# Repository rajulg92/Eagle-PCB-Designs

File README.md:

# Eagle-PCB-Designs
This Folder contains PCB designs both layout and Schematics for different Robotics sensors and Actuator interfaces. For example Pneumatics, Solenoid Valves, DC Motors and Drivers, BLDC Motors, Maxon Motors, PS2 Remote, etc.

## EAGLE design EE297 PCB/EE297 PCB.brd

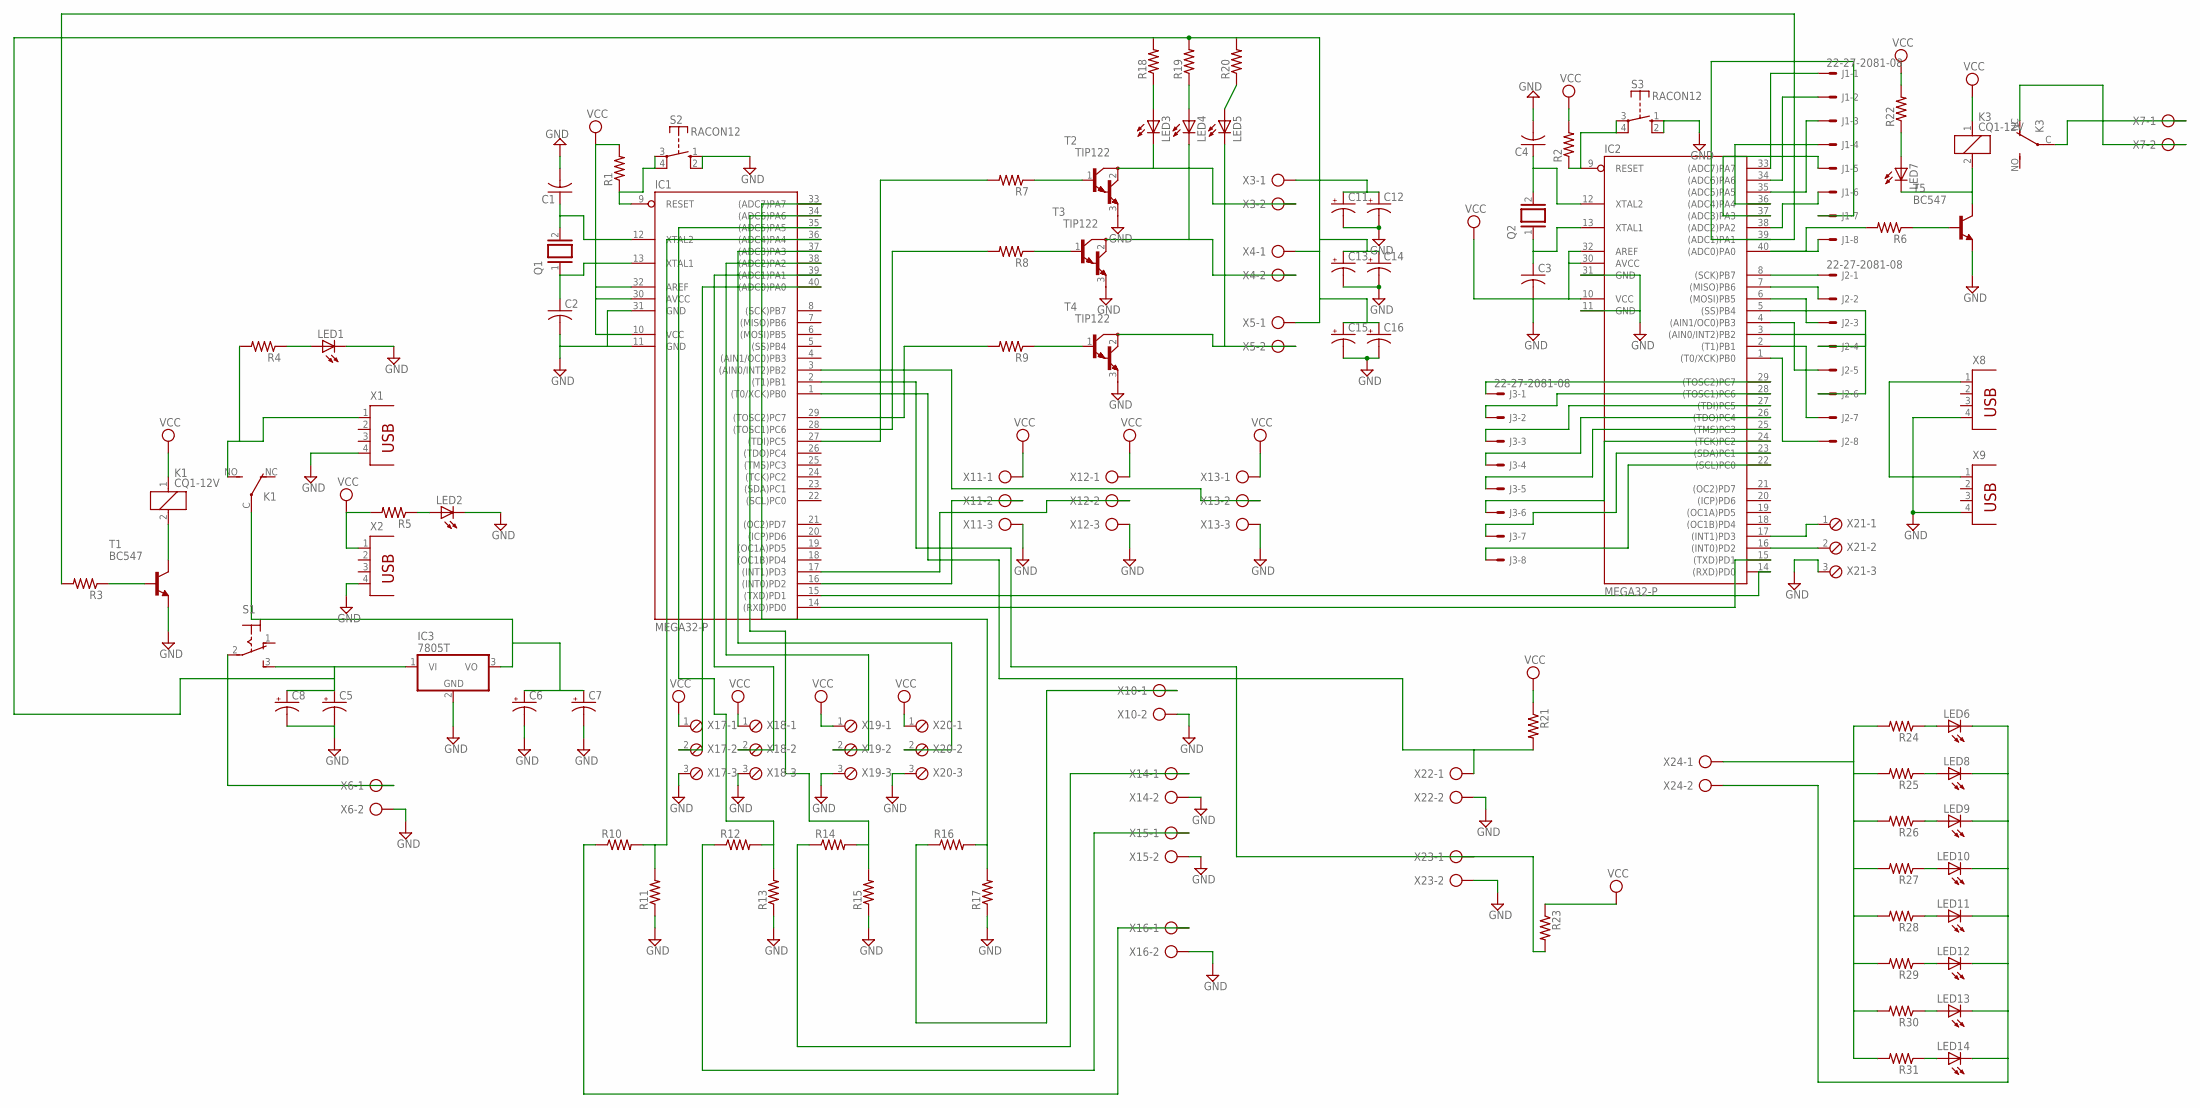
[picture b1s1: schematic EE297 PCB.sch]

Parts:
C1, C2, C3, C4: C-US050H075X075; C050H075X075
C5, C6, C7, C8, C11, C12, C13, C14, C15, C16: CPOL-USE7.5-18; E7,5-18
IC1, IC2: MEGA32-P; DIL40
IC3: 7805T; TO220H
J1, J2, J3: 22-27-2081-08; 6410-08
K1, K3: CQ1-12V; CQ1
LED1, LED2, LED3, LED4, LED5, LED6, LED7, LED8, LED9, LED10, LED11, LED12, LED13, LED14: LED5MM
Q1, Q2: XTAL; Q
R1, R2, R3, R4, R5, R6, R7, R8, R9, R10, R11, R12, R13, R14, R15, R16, R17, R18, R19, R20, R21, R22, R23, R24, R25, R26, R27, R28, R29, R30, R31: R-US_0207/10; 0207/10
S1: 320-916
S2, S3: RACON12
T1, T5: BC547; TO92
T2, T3, T4: TIP122; TO220
X1, X2, X8, X9: PN87520
X3, X4, X5, X6, X7, X10, X14, X15, X16, X22, X23, X24: AK300/2
X11, X12, X13: AK300/3
X17, X18, X19, X20, X21: MPT3; 3POL254

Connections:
GND: C1.2, C2.2, C3.2, C4.2, C5.-, C6.-, C7.-, C8.-, C11.-, C12.-, C13.-, C14.-, C15.-, C16.-, IC1.11 (GND), IC1.31 (GND), IC3.2 (GND), LED1.K (C), LED2.K (C), R11.1, R13.1, R15.1, R17.1, S2.1 (S), S2.2 (S), S3.1 (S), S3.2 (S), T1.1 (E), T2.3 (E), T3.3 (E), T4.3 (E), T5.1 (E), X1.4, X2.4, X6.2, X8.4, X9.4, X10.2, X11.3, X12.3, X13.3, X14.2, X15.2, X16.2, X17.3, X18.3, X19.3, X20.3, X21.3, X22.2, X23.2
GND8: LED6.K (C), LED8.K (C), LED9.K (C), LED10.K (C), LED11.K (C), LED12.K (C), LED13.K (C), LED14.K (C), X24.2
unnamed: S1.2, X6.1
unnamed: K3.C, X7.1
unnamed: C6.+, C7.+, IC3.3 (VO), K1.C
unnamed: IC1.14 ((RXD)PD0), IC2.15 ((TXD)PD1)
unnamed: R3.1, T1.2 (B)
unnamed: K1.2, T1.3 (C)
unnamed: K1.NO (S), R4.2, X1.1
unnamed: IC1.9 (RESET), R1.1, S2.3, S2.4
unnamed: IC1.1 ((T0/XCK)PB0), R21.2, X22.1
unnamed: C1.1, IC1.12 (XTAL2), Q1.2
unnamed: C2.1, IC1.13 (XTAL1), Q1.1
unnamed: IC1.15 ((TXD)PD1), IC2.14 ((RXD)PD0)
unnamed: IC1.40 ((ADC0)PA0), X17.2
unnamed: IC2.9 (RESET), R2.1, S3.3, S3.4
unnamed: IC1.39 ((ADC1)PA1), X18.2
unnamed: IC1.38 ((ADC2)PA2), X19.2
unnamed: C4.1, IC2.12 (XTAL2), Q2.2
unnamed: C3.1, IC2.13 (XTAL1), Q2.1
unnamed: IC1.37 ((ADC3)PA3), X20.2
unnamed: IC1.2 ((T1)PB1), R23.2, X23.1
unnamed: IC1.35 ((ADC5)PA5), R12.2, R13.2
unnamed: IC1.34 ((ADC6)PA6), R14.2, R15.2
unnamed: LED1.A, R4.1
unnamed: LED2.A, R5.1
unnamed: IC1.33 ((ADC7)PA7), R16.2, R17.2
unnamed: IC2.11 (GND), IC2.31 (GND)
unnamed: R6.1, T5.2 (B)
unnamed: K3.2, LED7.K (C), T5.3 (C)
unnamed: LED4.A, R19.1
unnamed: IC1.16 ((INT0)PD2), X11.2
unnamed: IC1.17 ((INT1)PD3), X12.2
unnamed: IC1.3 ((AIN0/INT2)PB2), X13.2
unnamed: IC1.29 ((TOSC2)PC7), R9.2
unnamed: IC1.28 ((TOSC1)PC6), R8.2
unnamed: IC1.27 ((TDI)PC5), R7.2
unnamed: R7.1, T2.1 (B)
unnamed: R8.1, T3.1 (B)
unnamed: R9.1, T4.1 (B)
unnamed: LED5.K (C), T4.2 (C), X5.2
unnamed: LED4.K (C), T3.2 (C), X4.2
unnamed: LED3.K (C), T2.2 (C), X3.2
unnamed: K3.NC (O), X7.2
unnamed: LED5.A, R20.1
unnamed: IC2.40 ((ADC0)PA0), J1.8, R6.2
unnamed: IC2.39 ((ADC1)PA1), J1.7, R3.2
unnamed: IC2.17 ((INT1)PD3), X21.1
unnamed: C5.+, C8.+, C11.+, C12.+, C13.+, C14.+, C15.+, C16.+, IC3.1 (VI), R18.2, R19.2, R20.2, S1.3 (S), X3.1, X4.1, X5.1
unnamed: IC2.16 ((INT0)PD2), X21.2
unnamed: X8.1, X9.1
unnamed: LED3.A, R18.1
unnamed: R10.1, X16.1
unnamed: R12.1, X15.1
unnamed: R14.1, X14.1
unnamed: R16.1, X10.1
unnamed: IC1.36 ((ADC4)PA4), R10.2, R11.2
unnamed: LED7.A, R22.1
unnamed: LED6.A, R24.1
unnamed: LED8.A, R25.1
unnamed: LED9.A, R26.1
unnamed: LED10.A, R27.1
unnamed: LED11.A, R28.1
unnamed: LED12.A, R29.1
unnamed: LED13.A, R30.1
unnamed: LED14.A, R31.1
unnamed: IC2.33 ((ADC7)PA7), J1.1
unnamed: IC2.34 ((ADC6)PA6), J1.2
unnamed: IC2.35 ((ADC5)PA5), J1.3
unnamed: IC2.36 ((ADC4)PA4), J1.4
unnamed: IC2.37 ((ADC3)PA3), J1.5
unnamed: IC2.38 ((ADC2)PA2), J1.6
unnamed: IC2.8 ((SCK)PB7), J2.1
unnamed: IC2.7 ((MISO)PB6), J2.2
unnamed: IC2.6 ((MOSI)PB5), J2.3
unnamed: IC2.5 ((SS)PB4), J2.4
unnamed: IC2.4 ((AIN1/OC0)PB3), J2.5
unnamed: IC2.3 ((AIN0/INT2)PB2), J2.6
unnamed: IC2.2 ((T1)PB1), J2.7
unnamed: IC2.1 ((T0/XCK)PB0), J2.8
unnamed: IC2.29 ((TOSC2)PC7), J3.1
unnamed: IC2.28 ((TOSC1)PC6), J3.2
unnamed: IC2.27 ((TDI)PC5), J3.3
unnamed: IC2.26 ((TDO)PC4), J3.4
unnamed: IC2.25 ((TMS)PC3), J3.5
unnamed: IC2.24 ((TCK)PC2), J3.6
unnamed: IC2.23 ((SDA)PC1), J3.7
unnamed: IC2.22 ((SCL)PC0), J3.8
VCC: IC1.10 (VCC), IC1.30 (AVCC), IC1.32 (AREF), IC2.10 (VCC), IC2.30 (AVCC), IC2.32 (AREF), K1.1, K3.1, R1.2, R2.2, R5.2, R21.1, R22.2, R23.1, X2.1, X11.1, X12.1, X13.1, X17.1, X18.1, X19.1, X20.1
VCC8: R24.2, R25.2, R26.2, R27.2, R28.2, R29.2, R30.2, R31.2, X24.1

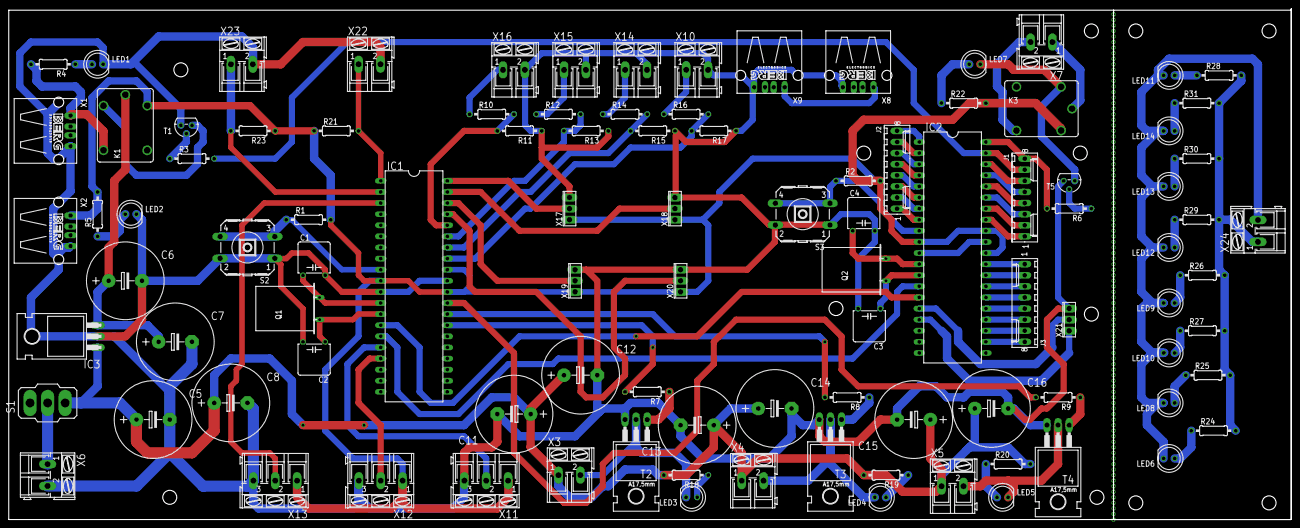
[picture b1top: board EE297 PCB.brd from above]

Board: 2 copper layers, 293.4 x 116.8 mm, 101 parts (0 on the bottom side), 90 nets.

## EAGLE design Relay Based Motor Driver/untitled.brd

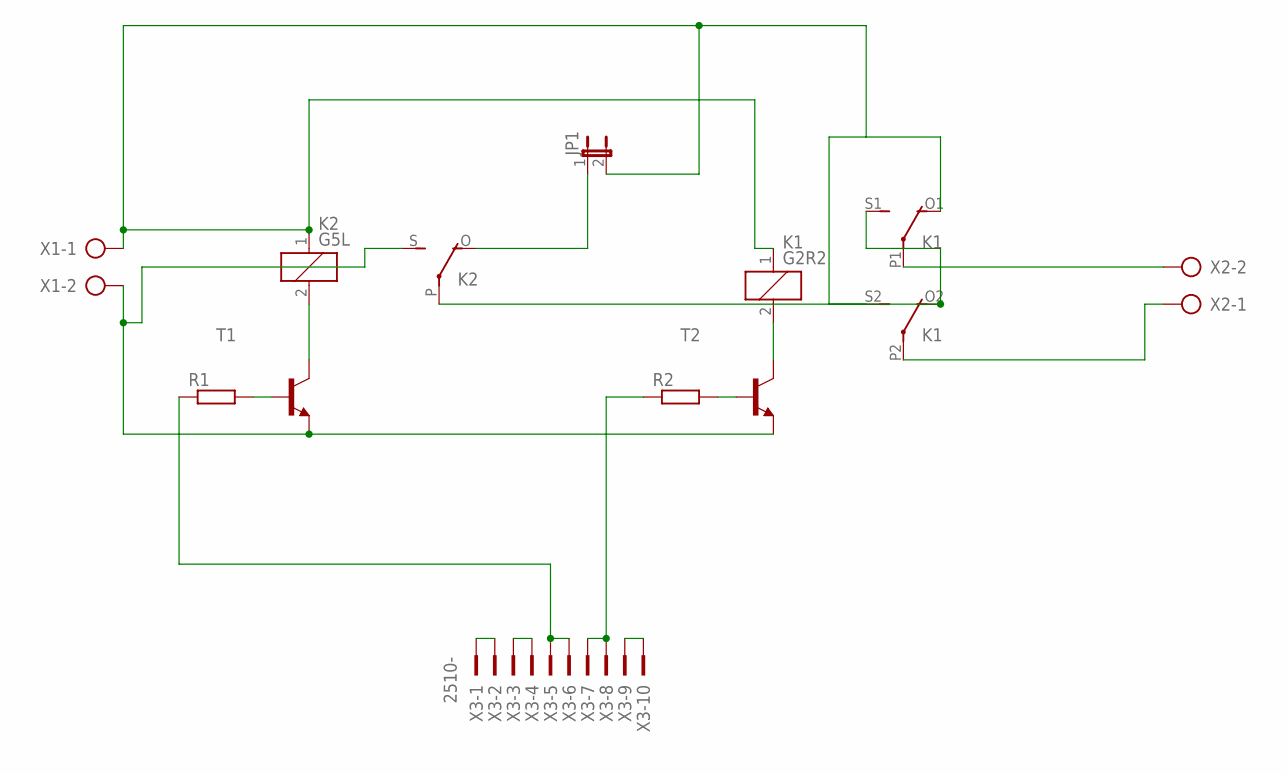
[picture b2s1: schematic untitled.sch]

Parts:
JP1: JP1E; JP1
K1: G2R2
K2: G5L; G5LE
R1, R2: R-EU_0207/10; 0207/10
T1, T2: 2N6517-NPN-TO92-CBE; TO92-CBE
X1, X2: AK300/2
X3: 2510-; PAK100/2500-10

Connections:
unnamed: K1.P1, X2.2
unnamed: K1.P2, X2.1
unnamed: K1.O2 (O), K1.S1 (S), K2.P
unnamed: K2.2, T1.C
unnamed: X3.1, X3.2
unnamed: X3.3, X3.4
unnamed: R1.1, X3.5, X3.6
unnamed: R2.1, X3.7, X3.8
unnamed: X3.9, X3.10
unnamed: R1.2, T1.B
unnamed: K2.S, T1.E, T2.E, X1.2
unnamed: JP1.1, K2.O
unnamed: R2.2, T2.B
unnamed: K1.2, T2.C
unnamed: JP1.2, K1.1, K1.O1 (O), K1.S2 (S), K2.1, X1.1

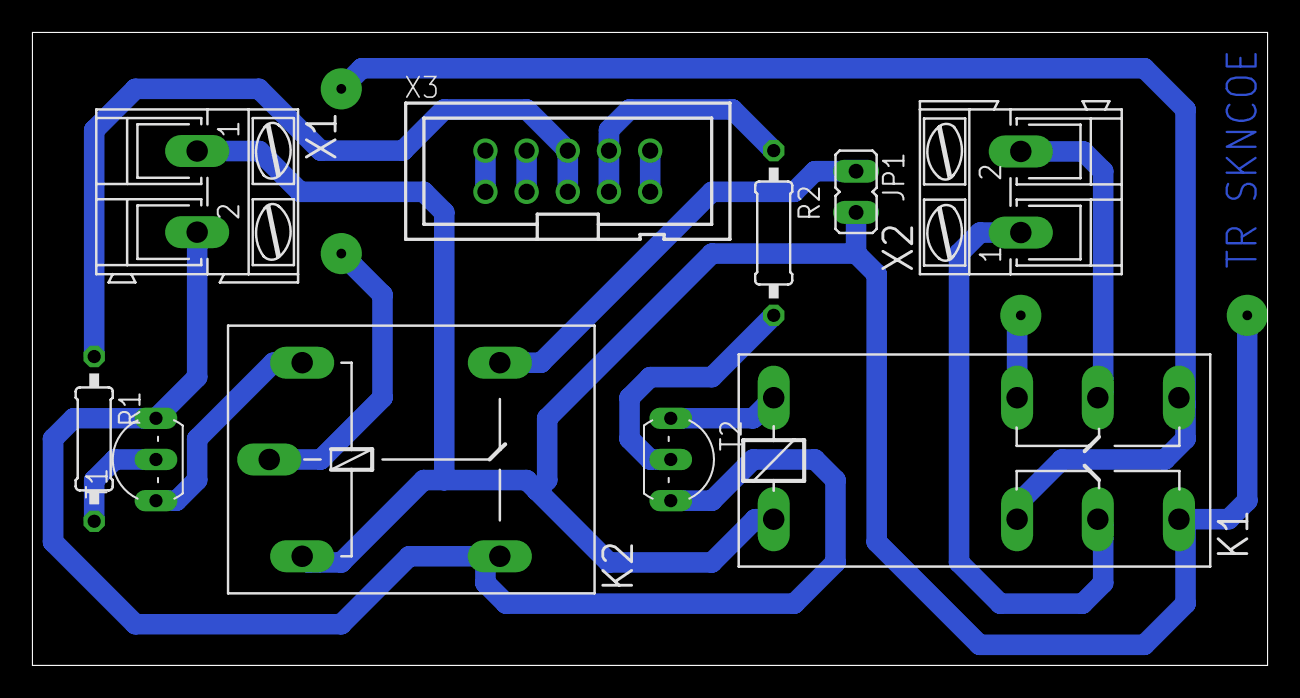
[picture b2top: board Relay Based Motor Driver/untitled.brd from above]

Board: 2 copper layers, 76.2 x 39.0 mm, 10 parts (0 on the bottom side), 15 nets.

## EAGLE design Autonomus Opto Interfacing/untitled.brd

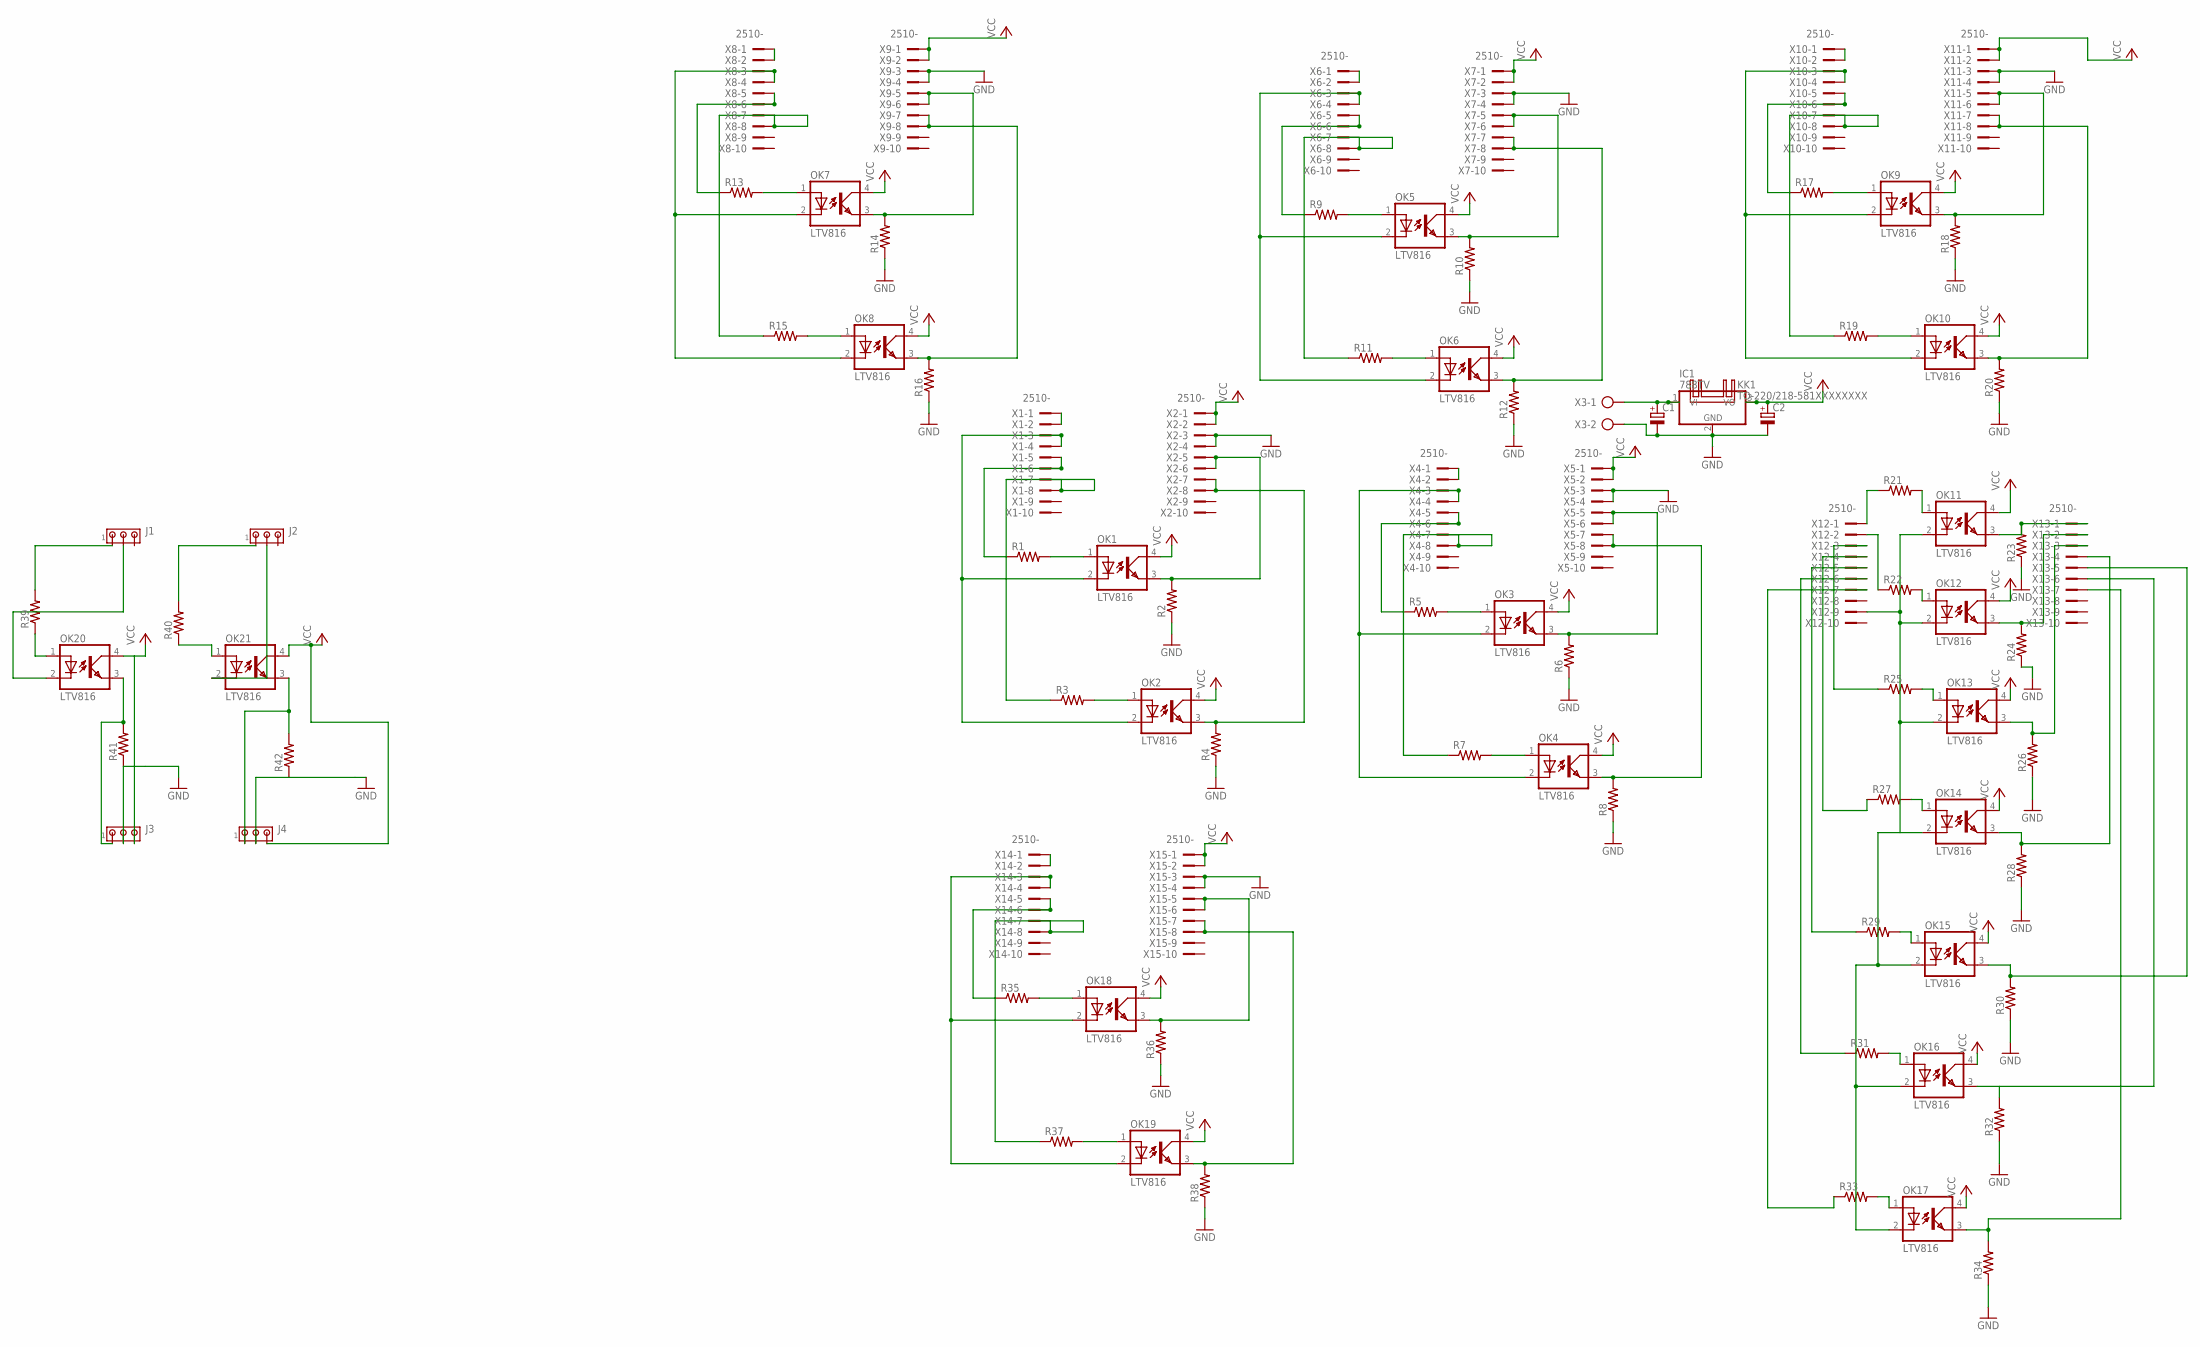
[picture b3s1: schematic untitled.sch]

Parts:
C1: CPOL-EUE5-13; E5-13
C2: CPOL-EUE5-10.5; E5-10,5
IC1: 788TV; TO220V
J1, J2, J3, J4: MTA03-100; 10X03MTA
KK1: TO-220/218-581XXXXXXXX; 581XXXXXXXX
OK1, OK2, OK3, OK4, OK5, OK6, OK7, OK8, OK9, OK10, OK11, OK12, OK13, OK14, OK15, OK16, OK17, OK18, OK19, OK20, OK21: LTV816; DIL04
R1, R2, R3, R4, R5, R6, R7, R8, R9, R10, R11, R12, R13, R14, R15, R16, R17, R18, R19, R20, R21, R22, R23, R24, R25, R26, R27, R28, R29, R30, R31, R32, R33, R34, R35, R36, R37, R38, R39, R40, R41, R42: R-US_0207/10; 0207/10
X1, X2, X4, X5, X6, X7, X8, X9, X10, X11, X12, X13, X14, X15: 2510-; PAK100/2500-10
X3: AK300/2

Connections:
GND: C1.-, C2.-, IC1.2 (GND), J3.2, J4.2, R2.1, R4.1, R6.1, R8.1, R10.1, R12.1, R14.1, R16.1, R18.1, R20.1, R23.1, R24.1, R26.1, R28.1, R30.1, R32.1, R34.1, R36.1, R38.1, R41.1, R42.1, X2.3, X2.4, X3.2, X5.3, X5.4, X7.3, X7.4, X9.3, X9.4, X11.3, X11.4, X15.3, X15.4
unnamed: X1.1, X1.2
unnamed: X4.1, X4.2
unnamed: R1.1, X1.5, X1.6
unnamed: R5.1, X4.5, X4.6
unnamed: C1.+, IC1.1 (VI), X3.1
unnamed: OK1.1 (A), R1.2
unnamed: OK3.1 (A), R5.2
unnamed: OK3.3 (EMIT), R6.2, X5.5, X5.6
unnamed: OK3.2 (C), OK4.2 (C), X4.3, X4.4
unnamed: OK1.3 (EMIT), R2.2, X2.5, X2.6
unnamed: R7.1, X4.7, X4.8
unnamed: OK1.2 (C), OK2.2 (C), X1.3, X1.4
unnamed: R3.1, X1.7, X1.8
unnamed: OK2.1 (A), R3.2
unnamed: OK2.3 (EMIT), R4.2, X2.7, X2.8
unnamed: OK4.1 (A), R7.2
unnamed: OK4.3 (EMIT), R8.2, X5.7, X5.8
unnamed: X6.1, X6.2
unnamed: R9.1, X6.5, X6.6
unnamed: OK5.1 (A), R9.2
unnamed: OK5.3 (EMIT), R10.2, X7.5, X7.6
unnamed: OK5.2 (C), OK6.2 (C), X6.3, X6.4
unnamed: R11.1, X6.7, X6.8
unnamed: OK6.1 (A), R11.2
unnamed: OK6.3 (EMIT), R12.2, X7.7, X7.8
unnamed: X8.1, X8.2
unnamed: R13.1, X8.5, X8.6
unnamed: OK7.1 (A), R13.2
unnamed: OK7.3 (EMIT), R14.2, X9.5, X9.6
unnamed: OK7.2 (C), OK8.2 (C), X8.3, X8.4
unnamed: R15.1, X8.7, X8.8
unnamed: OK8.1 (A), R15.2
unnamed: OK8.3 (EMIT), R16.2, X9.7, X9.8
unnamed: X10.1, X10.2
unnamed: R17.1, X10.5, X10.6
unnamed: OK9.1 (A), R17.2
unnamed: OK9.3 (EMIT), R18.2, X11.5, X11.6
unnamed: OK9.2 (C), OK10.2 (C), X10.3, X10.4
unnamed: R19.1, X10.7, X10.8
unnamed: OK10.1 (A), R19.2
unnamed: OK10.3 (EMIT), R20.2, X11.7, X11.8
unnamed: R21.1, X12.1
unnamed: OK11.1 (A), R21.2
unnamed: R22.1, X12.2
unnamed: OK12.1 (A), R22.2
unnamed: R25.1, X12.3
unnamed: OK13.1 (A), R25.2
unnamed: R33.1, X12.7
unnamed: OK11.3 (EMIT), R23.2, X13.1
unnamed: OK12.3 (EMIT), R24.2, X13.2
unnamed: OK13.3 (EMIT), R26.2, X13.3
unnamed: OK15.1 (A), R29.2
unnamed: OK14.1 (A), R27.2
unnamed: J1.1, R39.2
unnamed: OK14.3 (EMIT), R28.2, X13.4
unnamed: X14.1, X14.2
unnamed: OK15.3 (EMIT), R30.2, X13.5
unnamed: OK16.1 (A), R31.2
unnamed: OK16.3 (EMIT), R32.2, X13.6
unnamed: R35.1, X14.5, X14.6
unnamed: OK17.1 (A), R33.2
unnamed: OK11.2 (C), OK12.2 (C), OK13.2 (C), OK14.2 (C), OK15.2 (C), OK16.2 (C), OK17.2 (C), X12.9
unnamed: OK17.3 (EMIT), R34.2, X13.7
unnamed: R27.1, X12.4
unnamed: R29.1, X12.5
unnamed: R31.1, X12.6
unnamed: OK18.1 (A), R35.2
unnamed: OK18.3 (EMIT), R36.2, X15.5, X15.6
unnamed: OK18.2 (C), OK19.2 (C), X14.3, X14.4
unnamed: R37.1, X14.7, X14.8
unnamed: OK19.1 (A), R37.2
unnamed: OK19.3 (EMIT), R38.2, X15.7, X15.8
unnamed: OK20.1 (A), R39.1
unnamed: J1.2, OK20.2 (C)
unnamed: J3.1, OK20.3 (EMIT), R41.2
unnamed: J2.1, R40.2
unnamed: OK21.1 (A), R40.1
unnamed: J2.2, OK21.2 (C)
unnamed: J4.1, OK21.3 (EMIT), R42.2
VCC: C2.+, IC1.3 (VO), J3.3, J4.3, OK1.4 (COL), OK2.4 (COL), OK3.4 (COL), OK4.4 (COL), OK5.4 (COL), OK6.4 (COL), OK7.4 (COL), OK8.4 (COL), OK9.4 (COL), OK10.4 (COL), OK11.4 (COL), OK12.4 (COL), OK13.4 (COL), OK14.4 (COL), OK15.4 (COL), OK16.4 (COL), OK17.4 (COL), OK18.4 (COL), OK19.4 (COL), OK20.4 (COL), OK21.4 (COL), X2.1, X2.2, X5.1, X5.2, X7.1, X7.2, X9.1, X9.2, X11.1, X11.2, X15.1, X15.2

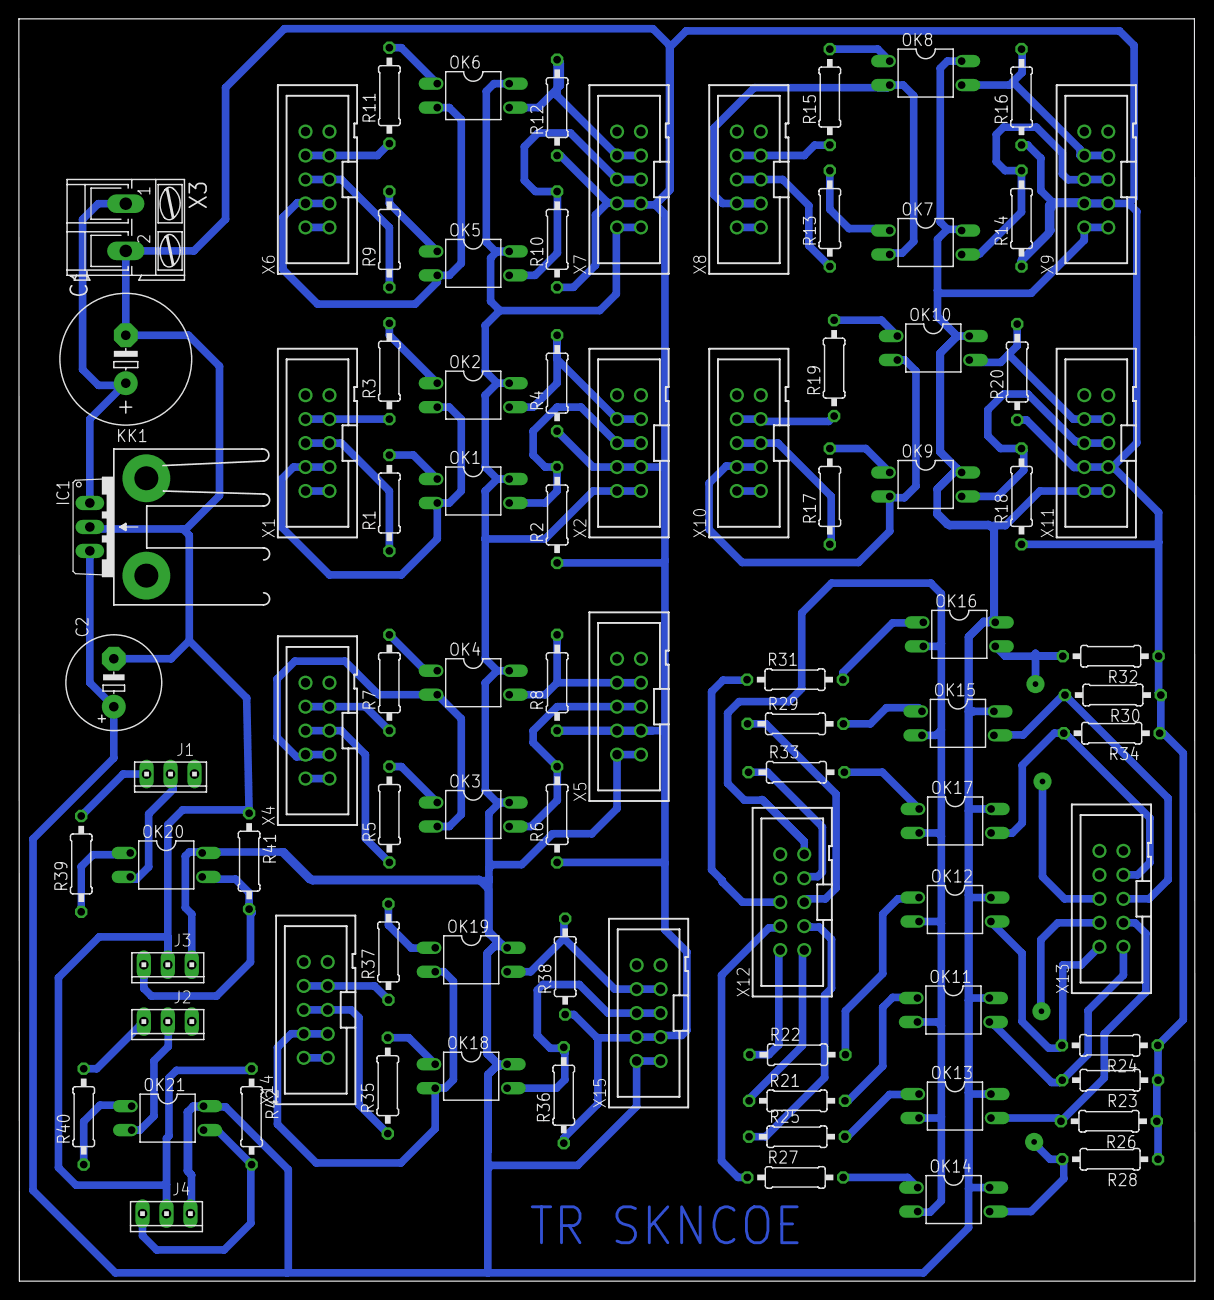
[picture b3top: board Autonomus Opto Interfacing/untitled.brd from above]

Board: 2 copper layers, 124.7 x 133.8 mm, 86 parts (0 on the bottom side), 81 nets.

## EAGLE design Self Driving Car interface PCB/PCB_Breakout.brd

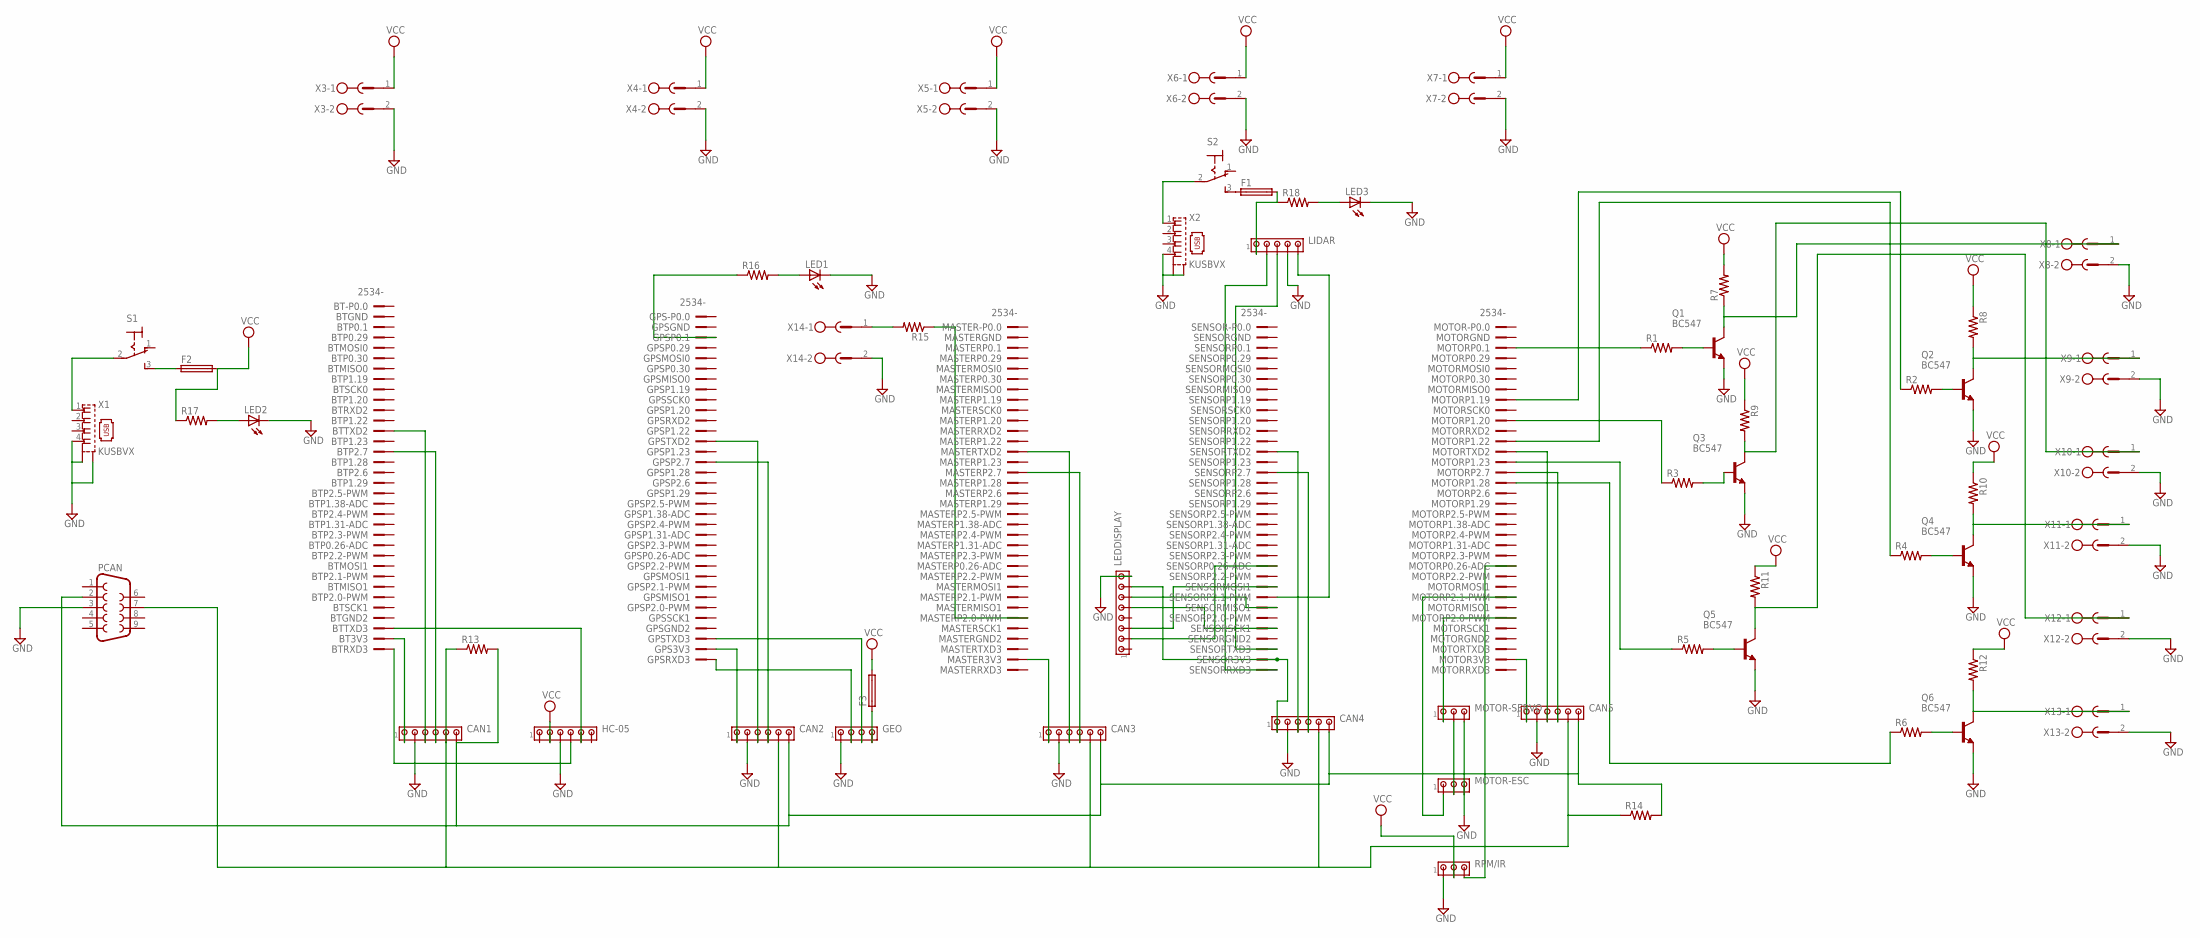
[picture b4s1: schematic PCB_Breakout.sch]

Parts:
BT: 2534-; PAK100/2500-34
CAN1, CAN2, CAN3, CAN4, CAN5: MTA06-100; 10X06MTA
F1, F2, F3: SH22,5
GEO: MTA04-100; 10X04MTA
GPS: 2534-; PAK100/2500-34
HC-05: MTA06-100; 10X06MTA
LED1, LED2, LED3: LED5MM
LEDDISPLAY: MTA08-100; 10X08MTA
LIDAR: MTA05-100; 10X05MTA
MASTER: 2534-; PAK100/2500-34
MOTOR: 2534-; PAK100/2500-34
MOTOR-ESC: MTA03-100; 10X03MTA
MOTOR-SERVO: MTA03-100; 10X03MTA
PCAN: F09HP
Q1, Q2, Q3, Q4, Q5, Q6: BC547; TO92
R1, R2, R3, R4, R5, R6, R7, R8, R9, R10, R11, R12, R13, R14, R15, R16, R17, R18: R-US_0207/10; 0207/10
RPM/IR: MTA03-100; 10X03MTA
S1, S2: M9040P
SENSOR: 2534-; PAK100/2500-34
X1, X2: KUSBVX
X3, X4, X5, X6, X7, X8, X9, X10, X11, X12, X13, X14: MSTBV2

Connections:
GND: CAN1.5 (2), CAN2.5 (2), CAN3.5 (2), CAN4.5 (2), CAN5.5 (2), GEO.1, HC-05.4 (3), LED1.K (C), LED2.K (C), LED3.K (C), LEDDISPLAY.8, LIDAR.4, MOTOR-ESC.3, MOTOR-SERVO.3, PCAN.3, Q1.1 (E), Q2.1 (E), Q3.1 (E), Q4.1 (E), Q5.1 (E), Q6.1 (E), RPM/IR.1, X1.4, X1.M1 (S1), X1.M2 (S2), X2.4, X2.M1 (S1), X2.M2 (S2), X3.2, X4.2, X5.2, X6.2, X7.2, X8.2, X9.2, X10.2, X11.2, X12.2, X13.2, X14.2
unnamed: S2.2, X2.1
unnamed: BT.33, CAN1.6 (1)
unnamed: CAN2.6 (1), GPS.33
unnamed: CAN3.6 (1), MASTER.33
unnamed: CAN4.6 (1), LEDDISPLAY.7, SENSOR.33
unnamed: CAN5.6 (1), MOTOR.33
unnamed: S1.2, X1.1
unnamed: F1.2, LIDAR.1, R18.1
unnamed: R15.2, X14.1
unnamed: MOTOR.3, R1.1
unnamed: MOTOR.8, R2.1
unnamed: MOTOR.10, R3.1
unnamed: MOTOR.12, R4.1
unnamed: MOTOR.14, R5.1
unnamed: MOTOR.16, R6.1
unnamed: Q5.2 (B), R5.2
unnamed: Q5.3 (C), R11.2, X12.1
unnamed: Q6.3 (C), R12.2, X13.1
unnamed: Q6.2 (B), R6.2
unnamed: Q4.2 (B), R4.2
unnamed: Q4.3 (C), R10.2, X11.1
unnamed: Q2.2 (B), R2.2
unnamed: Q2.3 (C), R8.2, X9.1
unnamed: Q1.3 (C), R7.1, X8.1
unnamed: Q1.2 (B), R1.2
unnamed: Q3.2 (B), R3.2
unnamed: Q3.3 (C), R9.2, X10.1
unnamed: MASTER.29, R15.1
unnamed: LED2.A, R17.2
unnamed: BT.13, CAN1.4 (3)
unnamed: BT.15, CAN1.3 (4)
unnamed: CAN2.4 (3), GPS.13
unnamed: CAN2.3 (4), GPS.15
unnamed: CAN3.4 (3), MASTER.13
unnamed: CAN3.3 (4), MASTER.15
unnamed: CAN4.4 (3), SENSOR.13
unnamed: CAN4.3 (4), SENSOR.15
unnamed: CAN5.4 (3), MOTOR.13
unnamed: CAN5.3 (4), MOTOR.15
unnamed: CAN1.2 (5), CAN2.2 (5), CAN3.2 (5), CAN4.2 (5), CAN5.2 (5), PCAN.7, R13.1, R14.1
unnamed: LED3.A, R18.2
unnamed: GPS.3, R16.1
unnamed: LED1.A, R16.2
unnamed: CAN1.1 (6), CAN2.1 (6), CAN3.1 (6), CAN4.1 (6), CAN5.1 (6), PCAN.2, R13.2, R14.2
unnamed: F2.1, S1.3 (S)
unnamed: F1.1, S2.3 (S)
unnamed: LIDAR.5, SENSOR.27
unnamed: MOTOR.29, MOTOR-SERVO.1
unnamed: MOTOR-ESC.2, MOTOR-SERVO.2
unnamed: MOTOR.27, MOTOR-ESC.1
unnamed: MOTOR.24, RPM/IR.3
unnamed: LIDAR.2, SENSOR.34
unnamed: LIDAR.3, SENSOR.32
unnamed: GEO.2, GPS.34
unnamed: GEO.3, GPS.32
unnamed: BT.34, HC-05.3 (4)
unnamed: BT.32, HC-05.2 (5)
unnamed: F3.1, GEO.4
unnamed: LEDDISPLAY.2, SENSOR.24
unnamed: LEDDISPLAY.3, SENSOR.26
unnamed: LEDDISPLAY.5, SENSOR.30
unnamed: LEDDISPLAY.6, SENSOR.28
VCC: F2.2, F3.2, HC-05.5 (2), R7.2, R8.1, R9.1, R10.1, R11.1, R12.1, R17.1, RPM/IR.2, X3.1, X4.1, X5.1, X6.1, X7.1

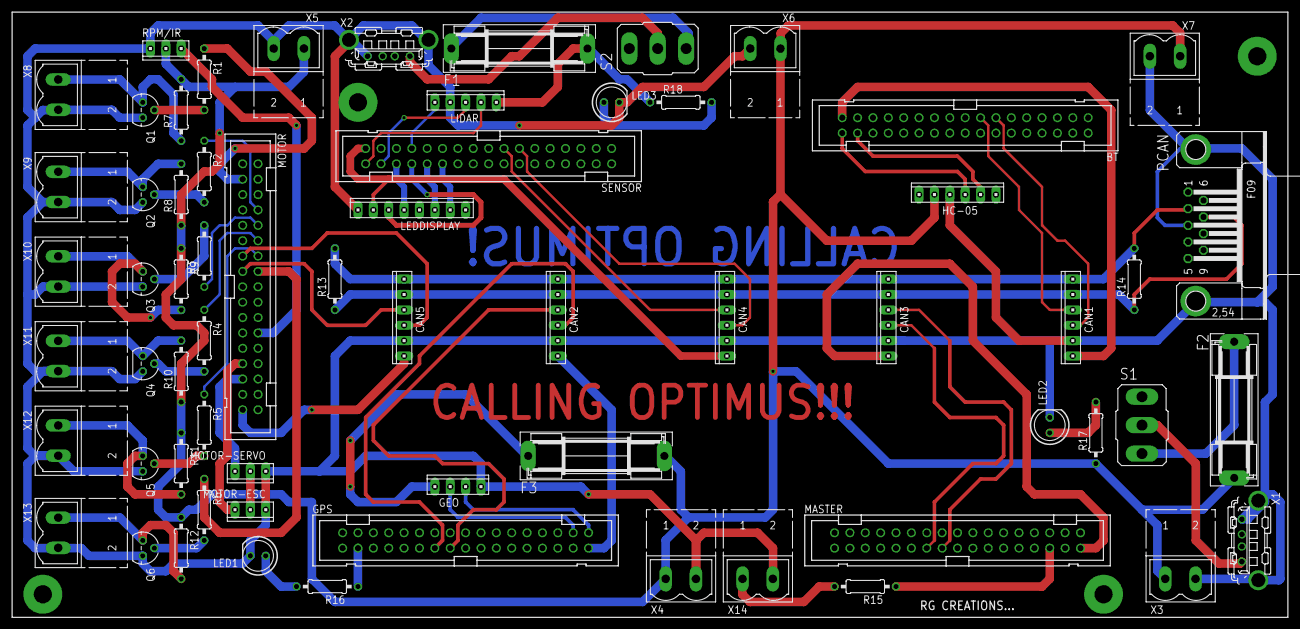
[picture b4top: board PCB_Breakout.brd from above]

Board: 2 copper layers, 210.8 x 100.0 mm, 64 parts (0 on the bottom side), 64 nets.

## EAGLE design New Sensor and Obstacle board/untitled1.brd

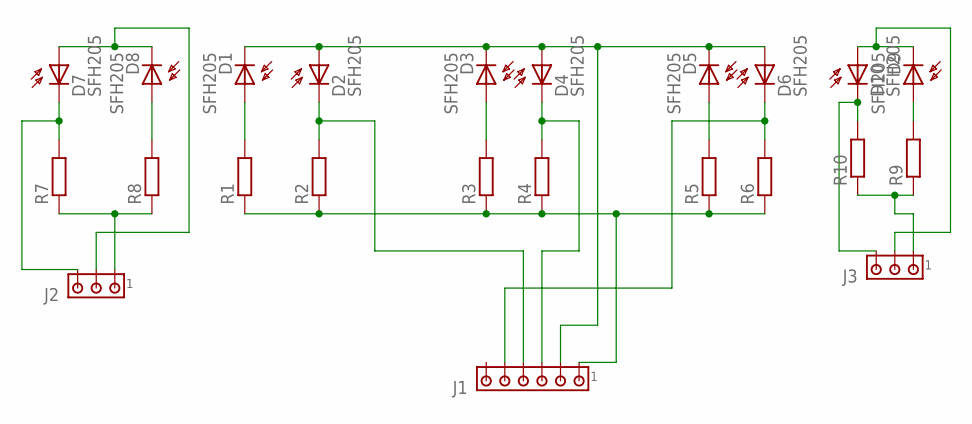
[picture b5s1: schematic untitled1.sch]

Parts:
D1, D2, D3, D4, D5, D6, D7, D8, D9, D10: SFH205
J1: MTA06-100; 10X06MTA
J2, J3: MTA03-100; 10X03MTA
R1, R2, R3, R4, R5, R6, R7, R8, R9, R10: R-EU_0207/10; 0207/10

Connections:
unnamed: D1.A, R1.2
unnamed: D9.K (C), D10.A, J3.2
unnamed: D3.A, R3.2
unnamed: D4.K (C), J1.4 (3), R4.2
unnamed: D5.A, R5.2
unnamed: D6.K (C), J1.2 (5), R6.2
unnamed: J1.6 (1), R1.1, R2.1, R3.1, R4.1, R5.1, R6.1
unnamed: D1.K (C), D2.A, D3.K (C), D4.A, D5.K (C), D6.A, J1.5 (2)
unnamed: D7.K (C), J2.3, R7.2
unnamed: D7.A, D8.K (C), J2.2
unnamed: D2.K (C), J1.3 (4), R2.2
unnamed: D8.A, R8.2
unnamed: D10.K (C), J3.3, R10.2
unnamed: D9.A, R9.2
unnamed: J2.1, R7.1, R8.1
unnamed: J3.1, R9.1, R10.1

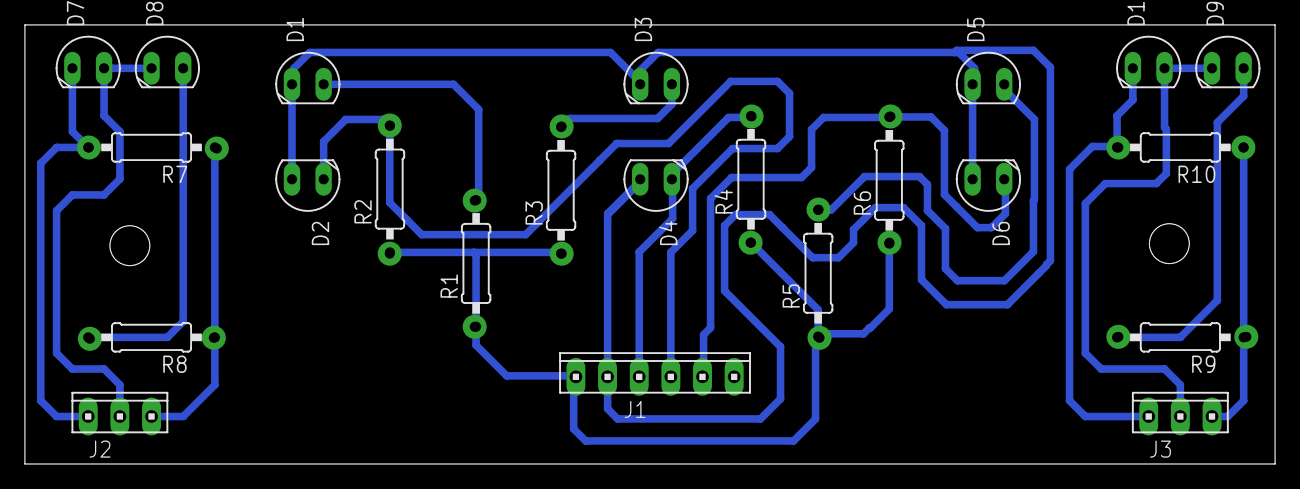
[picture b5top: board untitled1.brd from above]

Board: 2 copper layers, 100.3 x 35.2 mm, 23 parts (0 on the bottom side), 16 nets.

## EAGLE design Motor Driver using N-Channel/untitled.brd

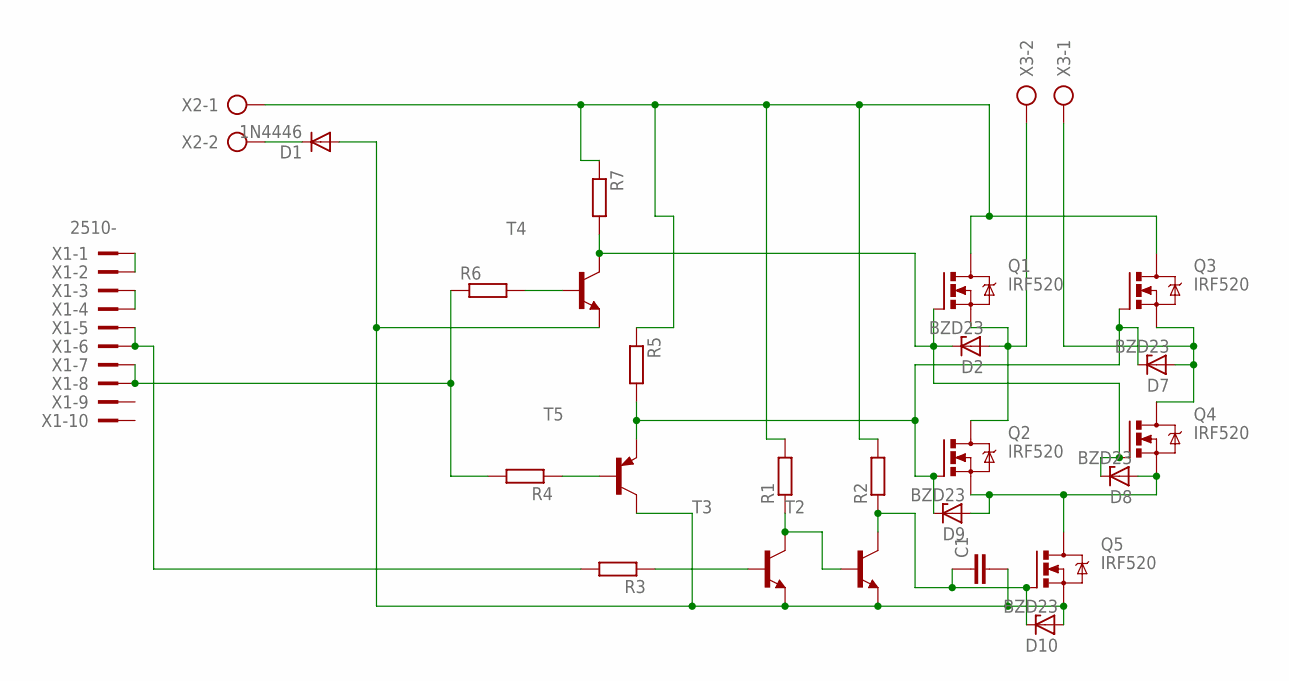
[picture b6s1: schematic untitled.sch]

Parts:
C1: C5/2.5; C5B2.5
D1: 1N4446; DO35-10
D2, D7, D8, D9, D10: BZD23; SOD81
Q1, Q2, Q3, Q4, Q5: IRF520; TO220BV
R1, R2, R3, R4, R5, R6, R7: R-EU_0207/10; 0207/10
T2, T3, T4: 2N4124-NPN-TO92-CBE; TO92-CBE
T5: BF493S-PNP-TO92-CBE; TO92-CBE
X1: 2510-; PAK100/2500-10
X2, X3: AK300/2

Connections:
unnamed: X1.1, X1.2
unnamed: X1.3, X1.4
unnamed: R3.2, X1.5, X1.6
unnamed: R4.2, R6.1, X1.7, X1.8
unnamed: C1.2, D1.A, D10.A, Q5.S, T2.E, T3.E, T4.E, T5.C
unnamed: R3.1, T3.B
unnamed: Q1.D, Q3.D, R1.2, R2.2, R5.1, R7.1, X2.1
unnamed: R1.1, T2.B, T3.C
unnamed: D1.C, X2.2
unnamed: D7.C, D9.C, Q2.G, Q3.G, R5.2, T5.E
unnamed: C1.1, D10.C, Q5.G, R2.1, T2.C
unnamed: R4.1, T5.B
unnamed: D2.A, Q1.S, Q2.D, X3.2
unnamed: R6.2, T4.B
unnamed: D8.A, D9.A, Q2.S, Q4.S, Q5.D
unnamed: D2.C, D8.C, Q1.G, Q4.G, R7.2, T4.C
unnamed: D7.A, Q3.S, Q4.D, X3.1

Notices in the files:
parts and their libraries:
heatsink-aavid: Copyright (C) 2004, Bob Starr (bobstarr@mindspring.com)
